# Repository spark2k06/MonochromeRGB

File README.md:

# MonochromeRGB

MonochromeRGB is a project to enjoy the charm of those monochrome monitors of the time but in the current video systems, those with VGA or SCART inputs. Where this product is most enjoyed is in CRT monitors, where the feeling of an old monitor is much more realistic.

https://hackaday.io/project/176201-monochromergb

Coworked with gambaman, when integrating the VGA2SCART module: 

https://hackaday.io/project/165634-the-ultimate-vga-to-scart-adapter

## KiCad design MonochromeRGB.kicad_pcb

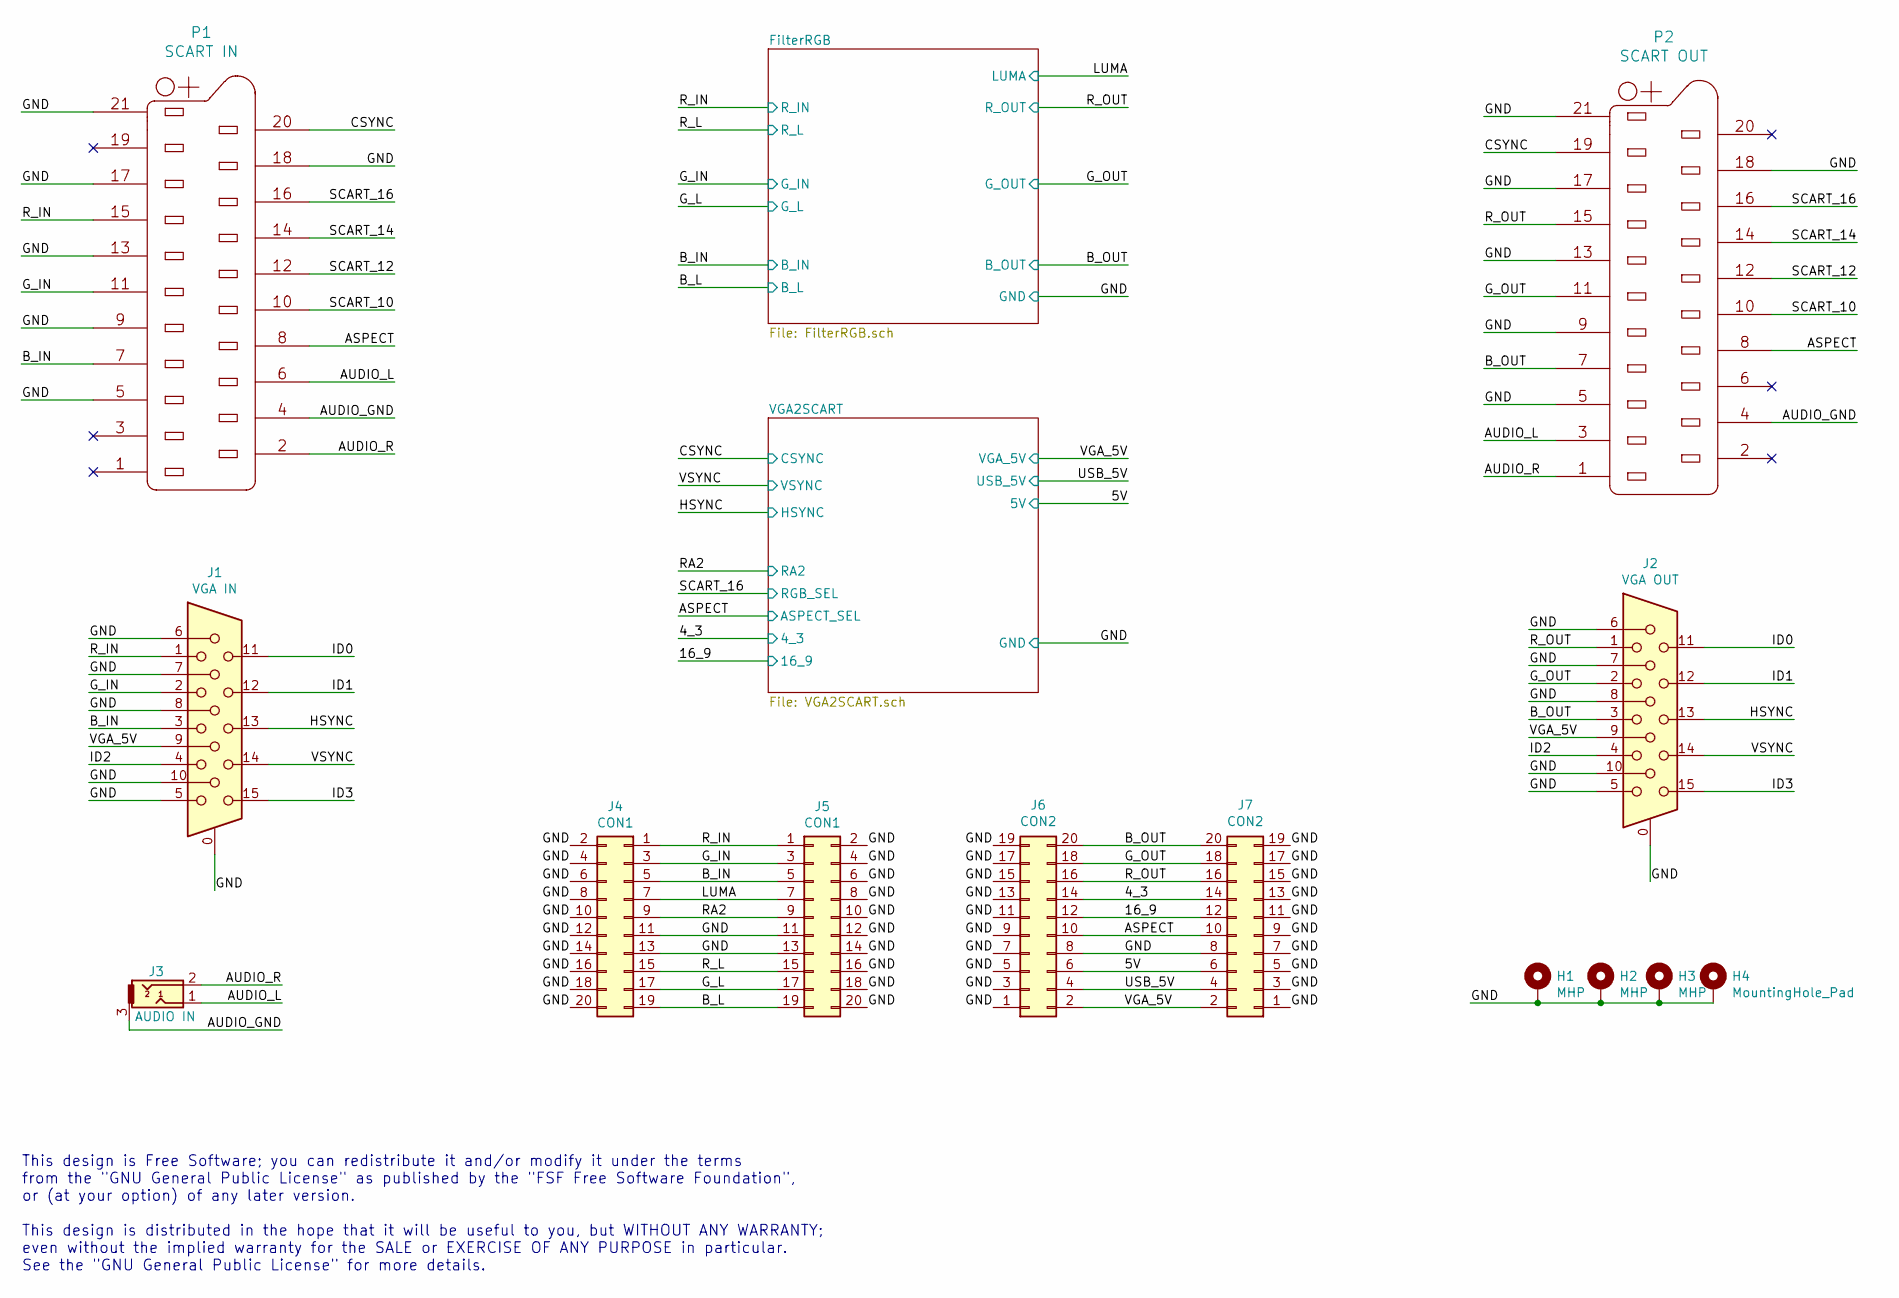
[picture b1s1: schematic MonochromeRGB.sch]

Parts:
H1, H2, H3: MHP; MountingHole_3.2mm_M3_Pad_Via
H4: MountingHole_Pad; MountingHole_3.2mm_M3_Pad_Via
J1: VGA IN; DSUB-15-HD_Female_Horizontal_P2.29x1.98mm_EdgePinOffset8.35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
J2: VGA OUT; DSUB-15-HD_Female_Horizontal_P2.29x1.98mm_EdgePinOffset8.35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
J3: AUDIO IN; SJ1-3523N-MvK
J4: CON1; PinHeader_2x10_P2.54mm_Vertical
J5: CON1; PinSocket_2x10_P2.54mm_Vertical
J6: CON2; PinHeader_2x10_P2.54mm_Vertical
J7: CON2; PinSocket_2x10_P2.54mm_Vertical
P1: SCART IN; SCART
P2: SCART OUT; SCART

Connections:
/4_3: J6.14, J7.14; also elsewhere on the board
/5V: J6.6, J7.6; also elsewhere on the board
/16_9: J6.12, J7.12; also elsewhere on the board
/ASPECT: J6.10, J7.10, P1.8, P2.8; also elsewhere on the board
/AUDIO_GND: J3.3, P1.4, P2.4
/AUDIO_L: J3.1, P1.6, P2.3
/AUDIO_R: J3.2, P1.2, P2.1
/B_IN: J1.3, J4.5, J5.5, P1.7; also elsewhere on the board
/B_L: J4.19, J5.19; also elsewhere on the board
/B_OUT: J2.3, J6.20, J7.20, P2.7; also elsewhere on the board
/CSYNC: P1.20, P2.19; also elsewhere on the board
/GND: H1.1, H2.1, H3.1, H4.1, J1.0, J1.5, J1.6, J1.7, J1.8, J1.10, J2.0, J2.5, J2.6, J2.7, J2.8, J2.10, J4.2, J4.4, J4.6, J4.8, J4.10, J4.11, J4.12, J4.13, J4.14, J4.16, J4.18, J4.20, J5.2, J5.4, J5.6, J5.8, J5.10, J5.11, J5.12, J5.13, J5.14, J5.16, J5.18, J5.20, J6.1, J6.3, J6.5, J6.7, J6.8, J6.9, J6.11, J6.13, J6.15, J6.17, J6.19, J7.1, J7.3, J7.5, J7.7, J7.8, J7.9, J7.11, J7.13, J7.15, J7.17, J7.19, P1.5, P1.9, P1.13, P1.17, P1.18, P1.21, P2.5, P2.9, P2.13, P2.17, P2.18, P2.21; also elsewhere on the board
/G_IN: J1.2, J4.3, J5.3, P1.11; also elsewhere on the board
/G_L: J4.17, J5.17; also elsewhere on the board
/G_OUT: J2.2, J6.18, J7.18, P2.11; also elsewhere on the board
/HSYNC: J1.13, J2.13; also elsewhere on the board
/ID0: J1.11, J2.11
/ID1: J1.12, J2.12
/ID2: J1.4, J2.4
/ID3: J1.15, J2.15
/LUMA: J4.7, J5.7; also elsewhere on the board
/RA2: J4.9, J5.9; also elsewhere on the board
/R_IN: J1.1, J4.1, J5.1, P1.15; also elsewhere on the board
/R_L: J4.15, J5.15; also elsewhere on the board
/R_OUT: J2.1, J6.16, J7.16, P2.15; also elsewhere on the board
/SCART_10: P1.10, P2.10
/SCART_12: P1.12, P2.12
/SCART_14: P1.14, P2.14
/SCART_16: P1.16, P2.16; also elsewhere on the board
/USB_5V: J6.4, J7.4; also elsewhere on the board
/VGA_5V: J1.9, J2.9, J6.2, J7.2; also elsewhere on the board
/VSYNC: J1.14, J2.14; also elsewhere on the board

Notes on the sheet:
This design is Free Software; you can redistribute it and/or modify it under the terms from the "GNU General Public License" as published by the "FSF Free Software Foundation", or (at your option) of any later version. This design is distributed in the hope that it will be useful to you, but WITHOU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

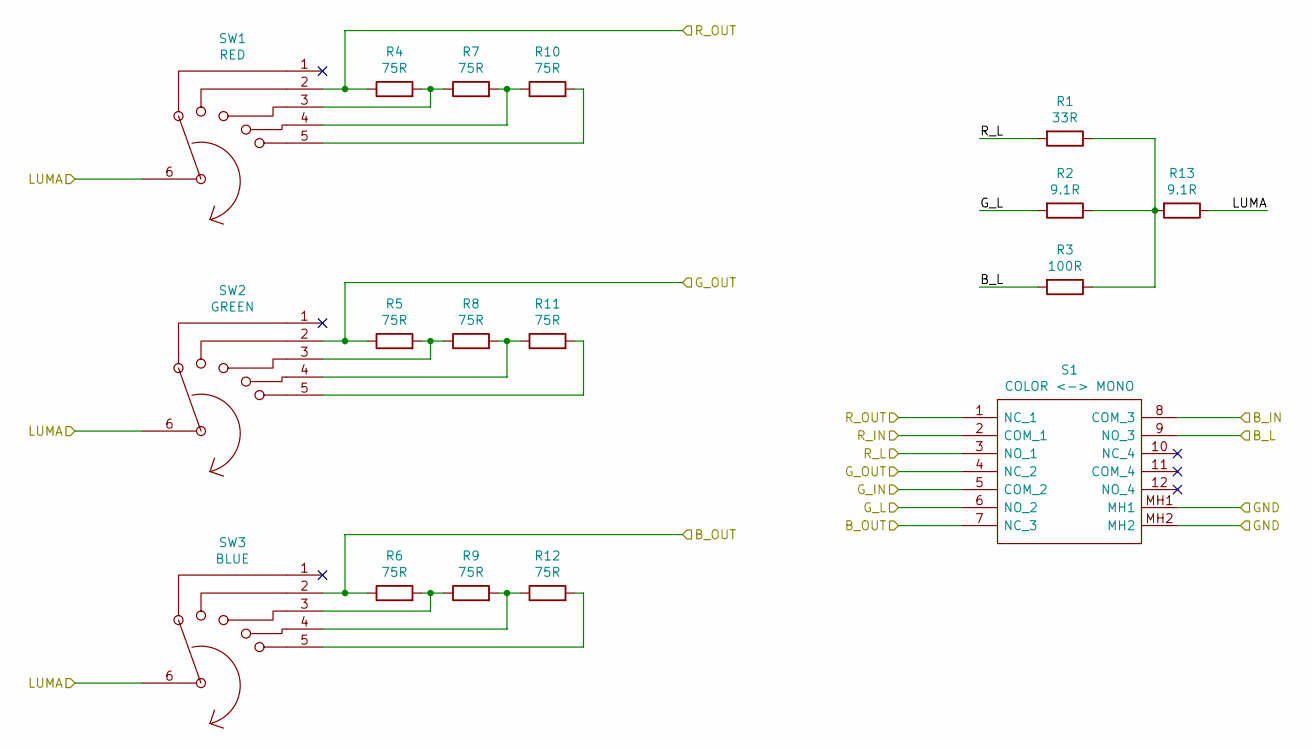
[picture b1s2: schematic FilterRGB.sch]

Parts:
R1: 33R; R_Axial_DIN0204_L3.6mm_D1.6mm_P5.08mm_Horizontal
R2, R13: 9.1R; R_Axial_DIN0204_L3.6mm_D1.6mm_P5.08mm_Horizontal
R3: 100R; R_Axial_DIN0204_L3.6mm_D1.6mm_P5.08mm_Horizontal
R4, R5, R6, R7, R8, R9, R10, R11, R12: 75R; R_Axial_DIN0204_L3.6mm_D1.6mm_P5.08mm_Horizontal
S1: COLOR <-> MONO; EG4208A; Mouser Part Number 612-EG4208A
SW1: RED; Rotary_Switch_1P5
SW2: GREEN; Rotary_Switch_1P5
SW3: BLUE; Rotary_Switch_1P5

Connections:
/B_IN: S1.8 (COM_3); also elsewhere on the board
/B_L: R3.2, S1.9 (NO_3); also elsewhere on the board
/B_OUT: R6.1, S1.7 (NC_3), SW3.2; also elsewhere on the board
/GND: S1.MH1, S1.MH2; also elsewhere on the board
/G_IN: S1.5 (COM_2); also elsewhere on the board
/G_L: R2.2, S1.6 (NO_2); also elsewhere on the board
/G_OUT: R5.1, S1.4 (NC_2), SW2.2; also elsewhere on the board
/LUMA: R13.1, SW1.6, SW2.6, SW3.6; also elsewhere on the board
/R_IN: S1.2 (COM_1); also elsewhere on the board
/R_L: R1.2, S1.3 (NO_1); also elsewhere on the board
/R_OUT: R4.1, S1.1 (NC_1), SW1.2; also elsewhere on the board
unnamed: R1.1, R2.1, R3.1, R13.2
unnamed: R4.2, R7.1, SW1.3
unnamed: R5.2, R8.1, SW2.3
unnamed: R6.2, R9.1, SW3.3
unnamed: R7.2, R10.1, SW1.4
unnamed: R10.2, SW1.5
unnamed: R8.2, R11.1, SW2.4
unnamed: R11.2, SW2.5
unnamed: R9.2, R12.1, SW3.4
unnamed: R12.2, SW3.5

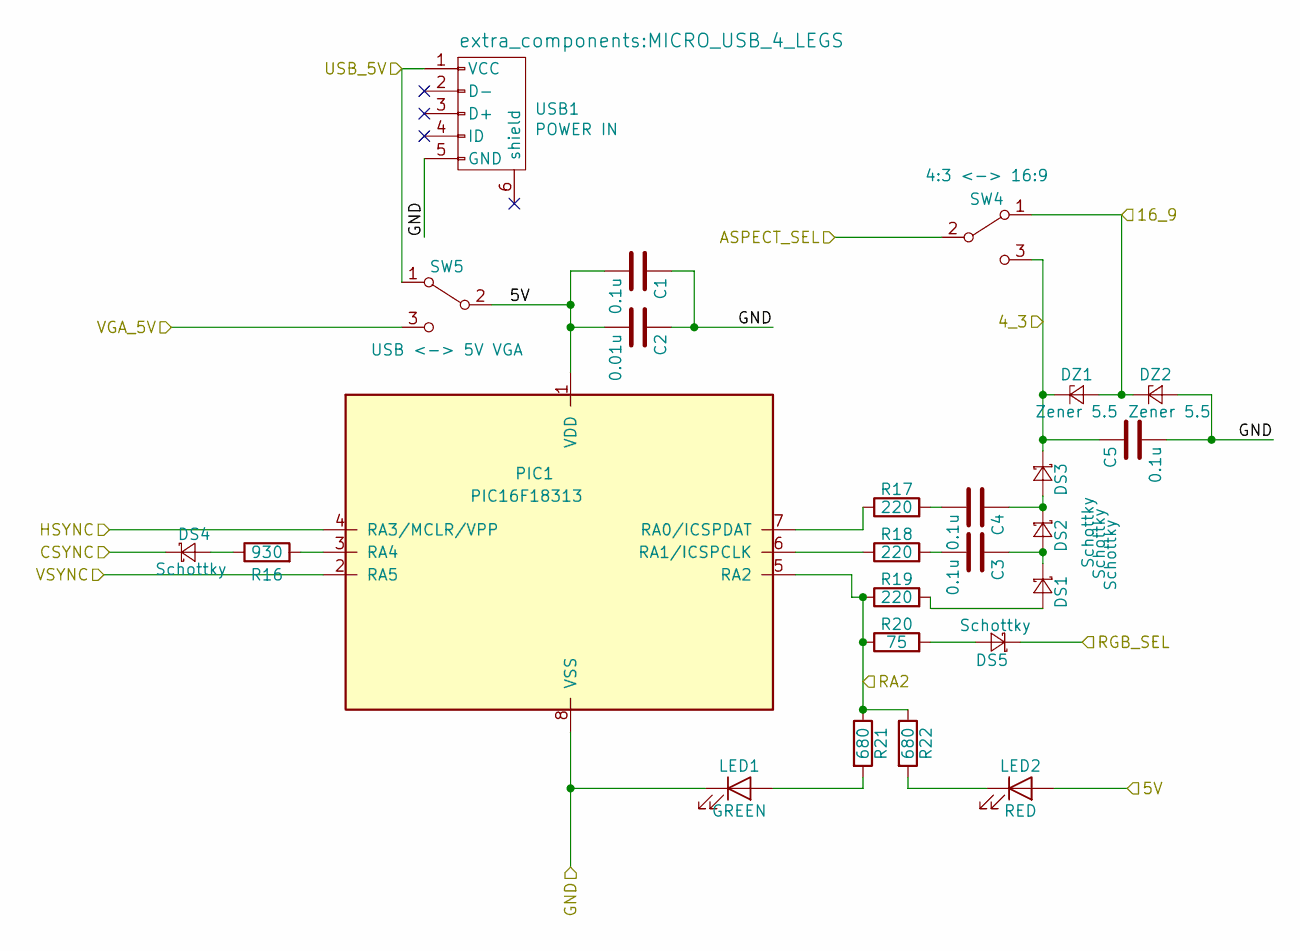
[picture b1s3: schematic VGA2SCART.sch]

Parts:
C1, C3, C4, C5: 0.1u; C_Disc_D4.3mm_W1.9mm_P5.00mm
C2: 0.01u; C_Disc_D4.3mm_W1.9mm_P5.00mm
DS1, DS2, DS3, DS4, DS5: Schottky; D_DO-41_SOD81_P7.62mm_Horizontal
DZ1, DZ2: Zener 5.5; D_DO-35_SOD27_P7.62mm_Horizontal
LED1: GREEN; LED_D1.8mm_W3.3mm_H2.4mm
LED2: RED; LED_D1.8mm_W3.3mm_H2.4mm
PIC1: PIC16F18313; DIP-8_W7.62mm
R16: 930; R_Axial_DIN0204_L3.6mm_D1.6mm_P5.08mm_Horizontal
R17, R18, R19: 220; R_Axial_DIN0204_L3.6mm_D1.6mm_P5.08mm_Horizontal
R20: 75; R_Axial_DIN0204_L3.6mm_D1.6mm_P5.08mm_Horizontal
R21, R22: 680; R_Axial_DIN0204_L3.6mm_D1.6mm_P5.08mm_Horizontal
SW4: 4:3 <-> 16:9; SW_CuK_OS102011MA1QN1_SPDT_Angled
SW5: USB <-> 5V VGA; SW_CuK_OS102011MA1QN1_SPDT_Angled
USB1: POWER IN; MICRO_USB_4_LEGS

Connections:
/4_3: C5.1, DS3.1 (K), DZ1.1 (K), SW4.3 (C); also elsewhere on the board
/5V: C1.2, C2.2, LED2.2 (A), PIC1.1 (VDD), SW5.2 (B); also elsewhere on the board
/16_9: DZ1.2 (A), DZ2.1 (K), SW4.1 (A); also elsewhere on the board
/ASPECT: SW4.2 (B); also elsewhere on the board
/CSYNC: DS4.1 (K); also elsewhere on the board
/GND: C1.1, C2.1, C5.2, DZ2.2 (A), LED1.1 (K), PIC1.8 (VSS), USB1.5 (GND); also elsewhere on the board
/HSYNC: PIC1.4 (RA3/MCLR/VPP); also elsewhere on the board
/RA2: PIC1.5 (RA2), R19.1, R20.1, R21.1, R22.1; also elsewhere on the board
/SCART_16: DS5.1 (K); also elsewhere on the board
/USB_5V: SW5.1 (A), USB1.1 (VCC); also elsewhere on the board
/VGA_5V: SW5.3 (C); also elsewhere on the board
/VSYNC: PIC1.2 (RA5); also elsewhere on the board
unnamed: C3.1, DS1.1 (K), DS2.2 (A)
unnamed: C3.2, R18.2
unnamed: C4.1, DS2.1 (K), DS3.2 (A)
unnamed: C4.2, R17.2
unnamed: DS1.2 (A), R19.2
unnamed: DS4.2 (A), R16.1
unnamed: DS5.2 (A), R20.2
unnamed: LED1.2 (A), R21.2
unnamed: LED2.1 (K), R22.2
unnamed: PIC1.3 (RA4), R16.2
unnamed: PIC1.6 (RA1/ICSPCLK), R18.1
unnamed: PIC1.7 (RA0/ICSPDAT), R17.1

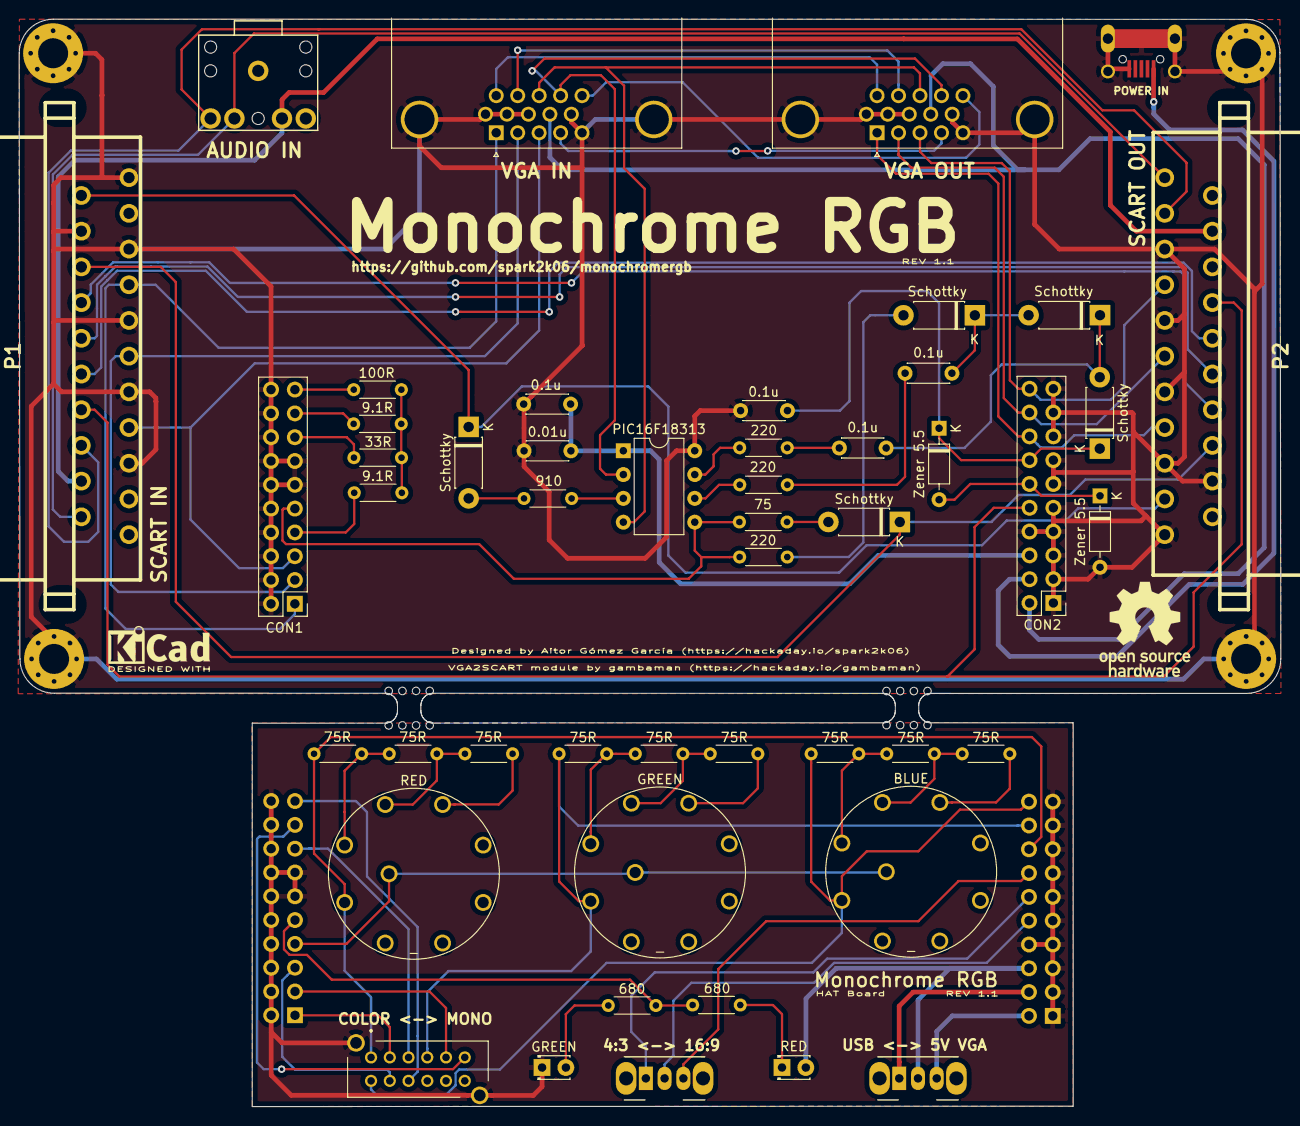
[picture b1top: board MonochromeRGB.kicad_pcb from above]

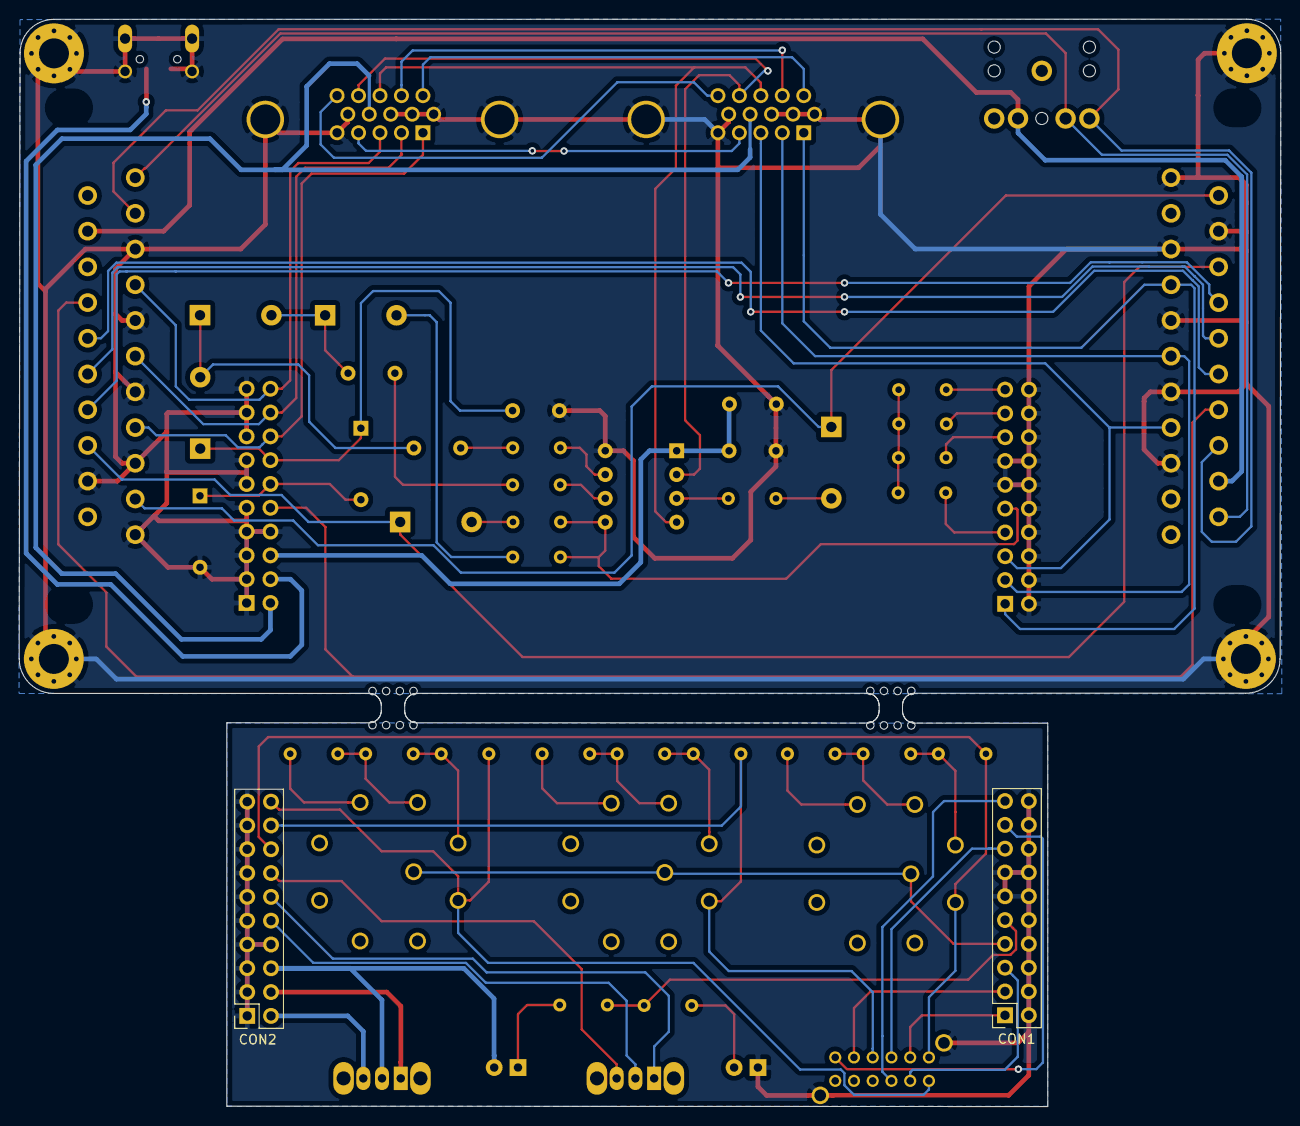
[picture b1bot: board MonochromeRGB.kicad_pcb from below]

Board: 2 copper layers, 134.6 x 116.0 mm, 55 parts (2 on the bottom side), 54 nets.

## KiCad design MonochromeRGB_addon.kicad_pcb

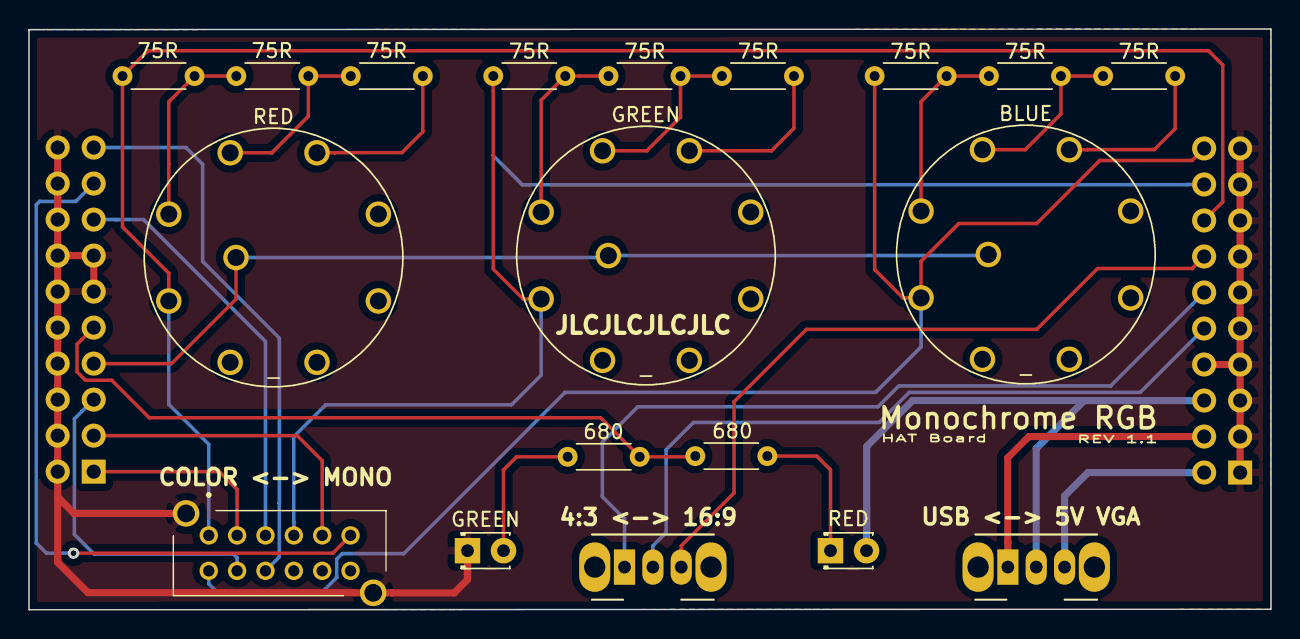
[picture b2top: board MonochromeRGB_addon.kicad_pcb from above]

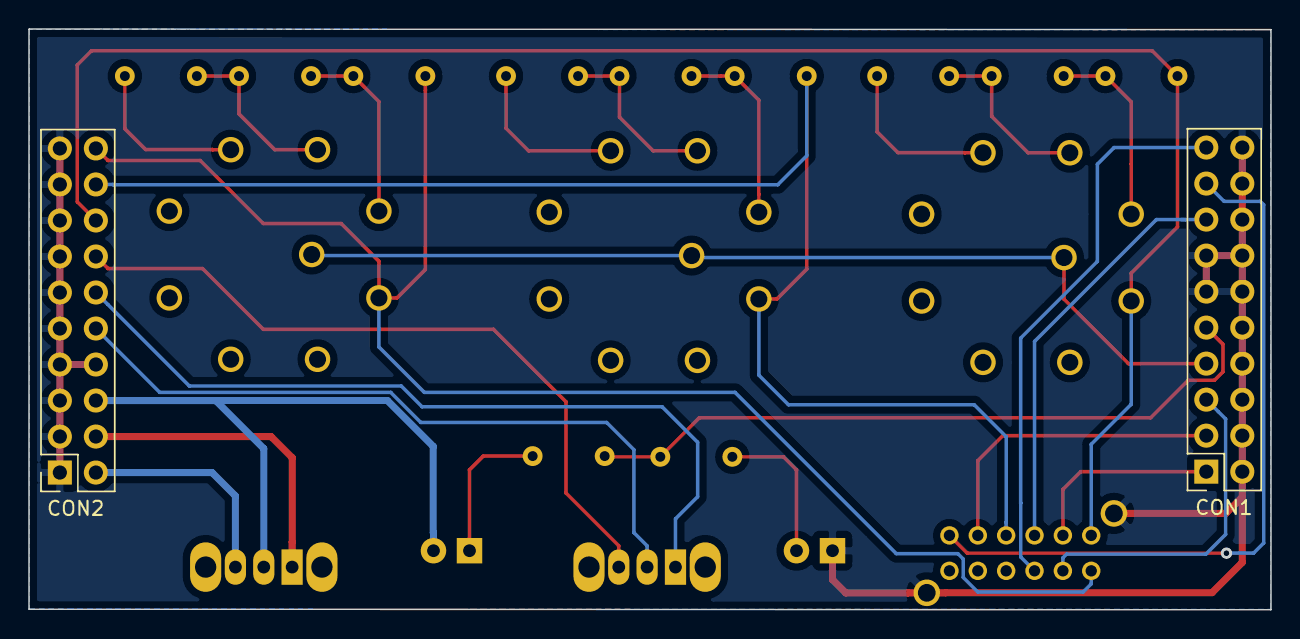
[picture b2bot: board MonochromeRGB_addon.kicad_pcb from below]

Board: 2 copper layers, 87.6 x 41.0 mm, 21 parts (2 on the bottom side), 29 nets.

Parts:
J5: CON1; PinSocket_2x10_P2.54mm_Vertical
J7: CON2; PinSocket_2x10_P2.54mm_Vertical
LED1: GREEN; LED_D1.8mm_W3.3mm_H2.4mm
LED2: RED; LED_D1.8mm_W3.3mm_H2.4mm
R4, R5, R6, R7, R8, R9, R10, R11, R12: 75R; R_Axial_DIN0204_L3.6mm_D1.6mm_P5.08mm_Horizontal
R21, R22: 680; R_Axial_DIN0204_L3.6mm_D1.6mm_P5.08mm_Horizontal
S1: COLOR <-> MONO; EG4208A
SW1: RED; Rotary_Switch_1P5
SW2: GREEN; Rotary_Switch_1P5
SW3: BLUE; Rotary_Switch_1P5
SW4: 4:3 <-> 16:9; SW_CuK_OS102011MA1QN1_SPDT_Angled
SW5: USB <-> 5V VGA; SW_CuK_OS102011MA1QN1_SPDT_Angled

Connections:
/4_3: J7.14, SW4.3
/5V: J7.6, LED2.2, SW5.2
/16_9: J7.12, SW4.1
/ASPECT: J7.10, SW4.2
/B_IN: J5.5, S1.8
/B_L: J5.19, S1.9
/B_OUT: J7.20, R6.1, S1.7, SW3.2
/GND: J5.2, J5.4, J5.6, J5.8, J5.10, J5.11, J5.12, J5.13, J5.14, J5.16, J5.18, J5.20, J7.1, J7.3, J7.5, J7.7, J7.8, J7.9, J7.11, J7.13, J7.15, J7.17, J7.19, LED1.1, S1.MH1, S1.MH2
/G_IN: J5.3, S1.5
/G_L: J5.17, S1.6
/G_OUT: J7.18, R5.1, S1.4, SW2.2
/LUMA: J5.7, SW1.6, SW2.6, SW3.6
/RA2: J5.9, R21.1, R22.1
/R_IN: J5.1, S1.2
/R_L: J5.15, S1.3
/R_OUT: J7.16, R4.1, S1.1, SW1.2
/USB_5V: J7.4, SW5.1
/VGA_5V: J7.2, SW5.3
unnamed: LED1.2, R21.2
unnamed: LED2.1, R22.2
unnamed: R4.2, R7.1, SW1.3
unnamed: R5.2, R8.1, SW2.3
unnamed: R6.2, R9.1, SW3.3
unnamed: R7.2, R10.1, SW1.4
unnamed: R10.2, SW1.5
unnamed: R8.2, R11.1, SW2.4
unnamed: R11.2, SW2.5
unnamed: R9.2, R12.1, SW3.4
unnamed: R12.2, SW3.5

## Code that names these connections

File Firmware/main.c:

/* VGA sync to SCART composite video sync generator
 * Copyright (C) 2019 David Guerrero
 *
 * Permission is hereby granted, free of charge, to any person obtaining a copy
 * of this software and associated documentation files (the "Software"), to deal
 * in the Software without restriction, including without limitation the rights
 * to use, copy, modify, merge, publish, distribute, sublicense, and/or sell
 * copies of the Software, and to permit persons to whom the Software is
 * furnished to do so, subject to the following conditions:
 *
 * The above copyright notice and this permission notice shall be included in
 * all copies or substantial portions of the Software.
 *
 * THE SOFTWARE IS PROVIDED "AS IS", WITHOUT WARRANTY OF ANY KIND, EXPRESS OR
 * IMPLIED, INCLUDING BUT NOT LIMITED TO THE WARRANTIES OF MERCHANTABILITY,
 * FITNESS FOR A PARTICULAR PURPOSE AND NONINFRINGEMENT. IN NO EVENT SHALL THE
 * AUTHORS OR COPYRIGHT HOLDERS BE LIABLE FOR ANY CLAIM, DAMAGES OR OTHER
 * LIABILITY, WHETHER IN AN ACTION OF CONTRACT, TORT OR OTHERWISE, ARISING FROM,
 * OUT OF OR IN CONNECTION WITH THE SOFTWARE OR THE USE OR OTHER DEALINGS IN
 * THE SOFTWARE.
 */

#include <pic.h>
#include <stdint.h>

// CONFIG1
#pragma config FEXTOSC = OFF // FEXTOSC External Oscillator mode Selection bits (Oscillator not enabled)
#pragma config RSTOSC = HFINT32 // Power-up default value for COSC bits (HFINTOSC with 2x PLL (32MHz))
#pragma config CLKOUTEN = OFF // Clock Out Enable bit (CLKOUT function is enabled; FOSC/4 clock appears at OSC2)
#pragma config CSWEN = ON // Clock Switch Enable bit (Writing to NOSC and NDIV is allowed)
#pragma config FCMEN = ON // Fail-Safe Clock Monitor Enable (Fail-Safe Clock Monitor is enabled)

// CONFIG2
#pragma config MCLRE = OFF // Master Clear Enable bit (MCLR/VPP pin function is digital input; MCLR internally disabled; Weak pull-up under control of port pin's WPU control bit.)
#pragma config PWRTE = ON // Power-up Timer Enable bit (PWRT enabled)
#pragma config WDTE = OFF // Watchdog Timer Enable bits (WDT disabled; SWDTEN is ignored)
#pragma config LPBOREN = OFF // Low-power BOR enable bit (ULPBOR disabled)
#pragma config BOREN = ON // Brown-out Reset Enable bits (Brown-out Reset enabled, SBOREN bit ignored)
#pragma config BORV = HIGH // Brown-out Reset Voltage selection bit (Brown-out voltage (Vbor) set to 2.45V)
#pragma config PPS1WAY = OFF // PPSLOCK bit One-Way Set Enable bit (The PPSLOCK bit can be cleared and set only once; PPS registers remain locked after one clear/set cycle)
#pragma config STVREN = ON // Stack Overflow/Underflow Reset Enable bit (Stack Overflow or Underflow will cause a Reset)
#pragma config DEBUG = OFF // Debugger enable bit (Background debugger disabled)


// CONFIG3
#pragma config WRT = OFF // User NVM self-write protection bits (Write protection off)
#pragma config LVP = OFF // Low Voltage Programming Enable bit (Low voltage programming enabled. MCLR/VPP pin function is MCLR. MCLRE configuration bit is ignored.)

// CONFIG4
#pragma config CP = OFF // User NVM Program Memory Code Protection bit (User NVM code protection disabled)
#pragma config CPD = OFF // Data NVM Memory Code Protection bit (Data NVM code protection disabled)

#define _XTAL_FREQ 32000000 //system clock frequency in hertzs
#define wave_FREQ 160000 //desired output wave frequency in hertzs
#define NCO_increment ((((uint32_t)wave_FREQ)<<11)/15625)//NCO clock will be HFINTOSC (16 MHz))
#define hsync_FREQ  15734 //Hsync nominal frequency in hertzs
#define hsync_normal_value LC1G3POL
#define vsync_pulsed_value LC1G1POL
#define hsync_value RA3
#define hsync_RA_number 3
#define vsync_value RA5
#define vsync_RA_number 5
#define enable RA2
#define enable_RA_number 2
#define cynscPPS RA4PPS
#define csync_RA_number 4
#define countdown_duration 740

void main(void)
{
    PORTA=0;
    TRISA=(1 << vsync_RA_number) | (1 << hsync_RA_number); //vsync and hsync input, everything else output
    ANSELA=0; //no analog inputs
    
    NCO1CLK=0;//NCO input clock is FINTOSC (16 MHz)
    NCO1INCU=NCO_increment>>16;
    NCO1INCH=NCO_increment>>8;
    NCO1INCL=NCO_increment;
    NCO1CON=0b10000000;//NCO enabled in fixed duty cycle mode
    
    CWG1DAT=0b00001001;//CWG clock source is NCO
    CWG1AS0=0b01101000;//Auto-Restart of CWG enabled. All waves=0 when disabled
    CWG1AS1=1;//CWG shutdowns only when pin CWG1PPS (enable signal) is low
    CWG1PPS=enable_RA_number;//CWG1PPS=enable signal
    RA0PPS=0b00001000;//RA0 pin is wave A
    RA1PPS=0b00001001;//RA1 pin is wave B
    CWG1CON0=0b10000100;//enable CWG in half-bridge mode.
    
    CLCIN0PPS=vsync_RA_number;//CLCIN0=vsync
    CLCIN1PPS=hsync_RA_number;//CLCIN1=hsync
    CLC1SEL0=0b00000000; //lc1d1T=CLCIN0 (vsync)
    CLC1SEL1=0b00000001; //lc1d2T=CLCIN1 (hsync)
    CLC1GLS0=0b00000010; //so lc1g1 will be lc1d1T=CLCIN0 (vsync)
    CLC1GLS1=0;          //so lc1g2 will be 0
    CLC1GLS2=0b00001000; //so lc1g3 will be lc1d3T=CLCIN1 (hsync)
    CLC1GLS3=0;          //so lc1g4 will be 0
    CLC1POL=0;           //nothing is inverted for now
    cynscPPS=0b00000100; //csync will be driven by the the output of the logic cell CLC1
    CLC1CON=0b10000001; //enable CLC output, disable CLC interrupts, set CLC functional mode at OR-XOR
    INTPPS=hsync_RA_number;//external interrupt source is hsync
    
    //tmr2 will be used to measure the period of hsync. Note that tmr2 prescaler source fequency is _XTAL_FREQ/4
    PR2=11*_XTAL_FREQ/hsync_FREQ/10/16;//set PR2 to the maximun acceptable hsync period
    PIE1bits.TMR2IE=1;//enables tmr2 match interrupt to detect if the period is too high. Does not matter if executed at the begining
    TMR2=0;
    T2CON=0b00000101;//activates tmr2, sets postcaler to 1:1 and prescaler to 1:4
    INTCON=0b11010000;//Enable global interrupts and peripheral interrupts (for tmr2 comparation match), external interrupt at the falling edge of hsync
    PIE0=0b00000001;//Enable external interrupt
    while(1);
}

__interrupt() void isr(void)
{  
    static uint16_t activation_countdown=countdown_duration;
    static uint16_t vsync_highs=0;
    PIR0bits.INTF=0;//clear external interrupt flag. Does not matter if this is being executed because of TMR2 overflow
    uint8_t hsync_period=TMR2;
    TMR2=0;
    __delay_us(300000/hsync_FREQ);//wait for a 30% of the nominal period to make sure hsync is not pulsed before reading it
    CLC1POLbits.hsync_normal_value=PORTAbits.hsync_value;//this has no efect if the previos value is the same, otherwise reconfigure the CLC for the correct polarity of the hsync pulses
    /////now check if the input sync signals are OK
    if( 
            hsync_period<=9*_XTAL_FREQ/hsync_FREQ/10/16 //hsync frequency is too high
        ||  PIR1bits.TMR2IF //hsync frequency is too low
        ||  (activation_countdown==0 && (vsync_highs==0 || vsync_highs==countdown_duration))//vsync is not changing
      )//something is wrong. Csync must be disabled
        {   
            CLC1CONbits.LC1EN=0;//fix CLC output to 0
            PORTAbits.enable=0;//set the enable output signal to 0
            activation_countdown=countdown_duration;
            vsync_highs=0;
        }
    /////now enable csync at the end of the countdown check if the input sync signals are OK
    if(activation_countdown)
        {//This is executed countdown_duration times before activation
            vsync_highs+=PORTAbits.vsync_value;//count the number of times vsync is high
            activation_countdown--;
        }
    else
        {//end of countdown reached. Csync must be enabled
            CLC1POLbits.vsync_pulsed_value= vsync_highs<countdown_duration/2;//inverts vsync if necessary
            CLC1CONbits.LC1EN=1;//so the CLC output can change
            PORTAbits.enable=1;//set the enable output signal to 1
            activation_countdown=countdown_duration;//Vsync must be measured periodically
            vsync_highs=0;                          //because the video mode can change
        }
    PIR1bits.TMR2IF=0;
}

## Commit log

2020-12-20 Version 1.1
2020-12-20 Mencion to Gambaman and the module VGA2SCART
2020-12-20 Thanks to Gambaman and the module VGA2SCART
2020-12-21 CERN-OHL-W licence
2020-12-21 Update licenses
